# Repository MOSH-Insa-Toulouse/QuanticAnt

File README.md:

# Projet_MOSH 

Auteurs : Quentin Martinez, Nicolas Baudeau, Soufian Yjjou

Caractéristiques de "QuanticAnt" :

Basé sur une arduino, QuanticAnt est un "robot" de petite taille équipé de 4 pattes lui permettant de se déplacer sur le sol.
Les solutions de détections lui permettent d'éviter les obstacles et d'évoluer de façon aléatoire dans une pièce.

QuanticAnt est repoussé par la lumière et emet un son aggaçant quand il se sent bien (peu de lumière ambiante).
Pour prendre le controle de cet insecte l'éclairer directement le force vers une direction donnée.

Mots clés : MARCHE ALEATOIRE, LUMIERE, SANS ROUES, DETECTION D'OBSTACLES

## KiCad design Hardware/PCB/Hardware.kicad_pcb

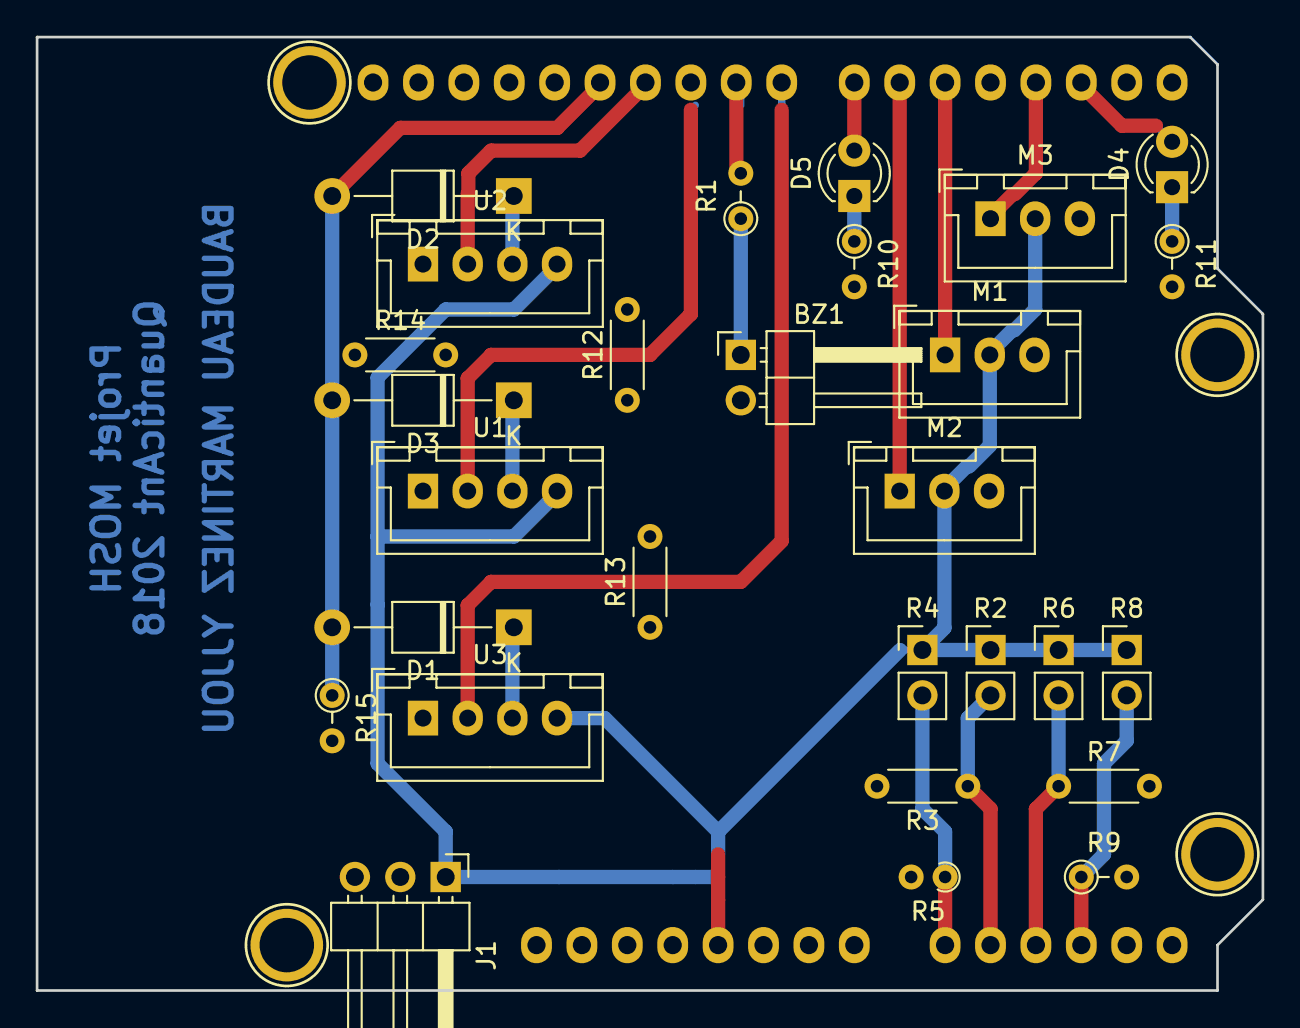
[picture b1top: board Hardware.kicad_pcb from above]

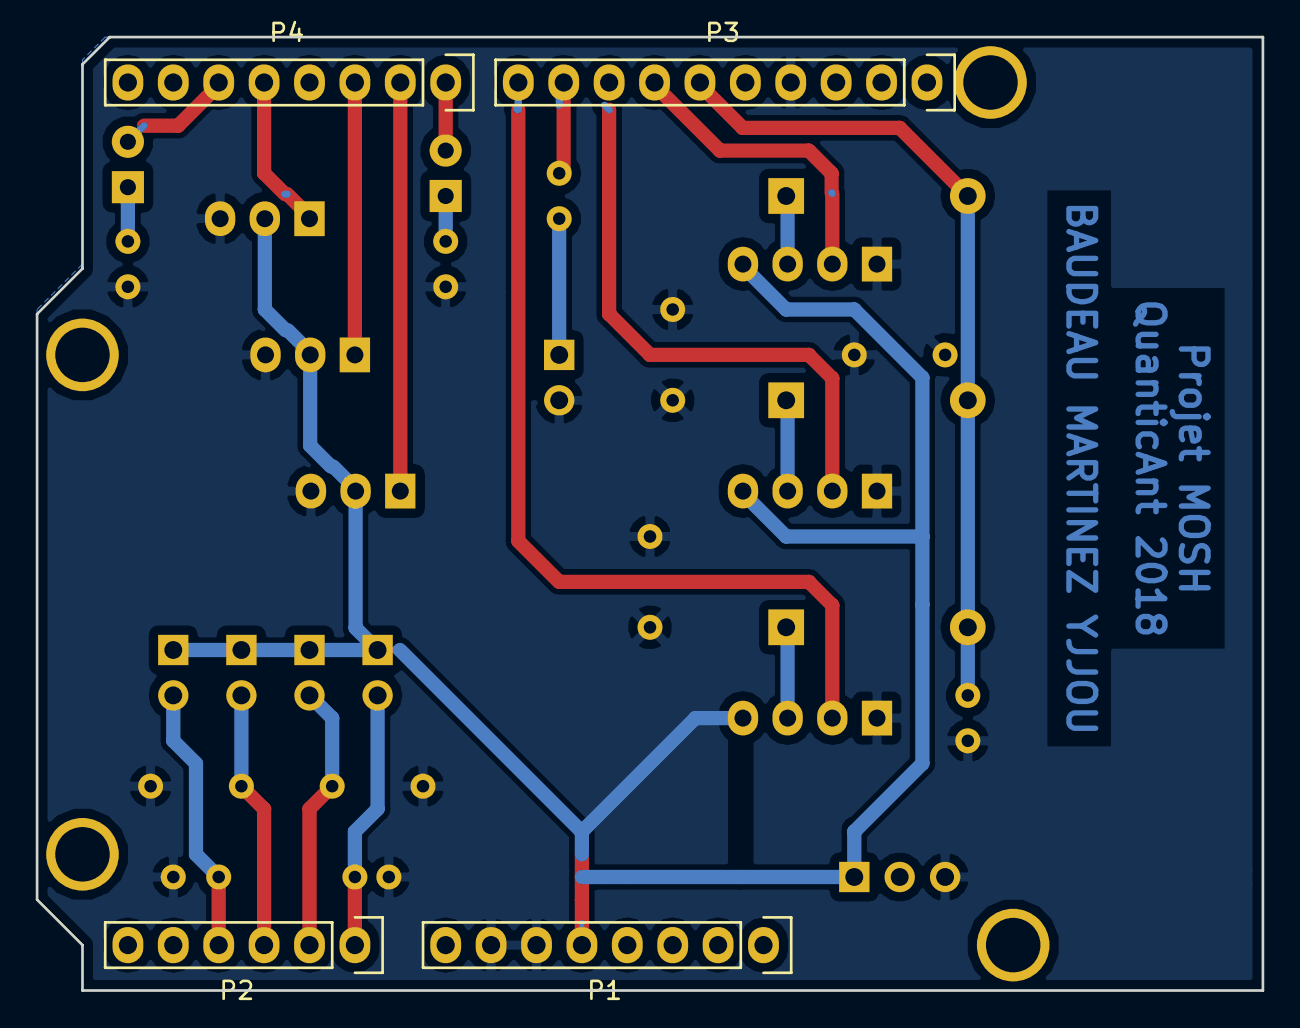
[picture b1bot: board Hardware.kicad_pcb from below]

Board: 2 copper layers, 68.6 x 53.3 mm, 36 parts (4 on the bottom side), 24 nets.

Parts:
BZ1: Buzzer; PinHeader_1x02_P2.54mm_Horizontal
D1, D2, D3: DIODE; D_T-1_P10.16mm_Horizontal
D4, D5: LED; LED_D3.0mm
J1: Conn_01x03_Male; PinHeader_1x03_P2.54mm_Horizontal
M1, M2, M3: Motor_Servo; JST_XH_B03B-XH-A_1x03_P2.50mm_Vertical
P1: Power; Socket_Strip_Arduino_1x08
P2: Analog; Socket_Strip_Arduino_1x06
P3: Digital; Socket_Strip_Arduino_1x10
P4: Digital; Socket_Strip_Arduino_1x08
P5, P6, P7, P8: CONN_01X01; Arduino_1pin
R1, R9, R10, R11, R15: R; R_Axial_DIN0204_L3.6mm_D1.6mm_P2.54mm_Vertical
R2, R4, R6, R8: LDR03; PinHeader_1x02_P2.54mm_Vertical
R3, R7, R12, R13, R14: R; R_Axial_DIN0204_L3.6mm_D1.6mm_P5.08mm_Horizontal
R5: R; R_Axial_DIN0204_L3.6mm_D1.6mm_P1.90mm_Vertical
U1, U2, U3: HC-SR04; JST_XH_B04B-XH-A_1x04_P2.50mm_Vertical

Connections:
+5V: J1.1, M1.2, M2.2, M3.2, P1.5, R2.1, R4.1, R6.1, R8.1, U1.4, U2.4, U3.4
/2: D4.2, P4.6
/3(**): M3.1, P4.5
/5(**): M1.1, P4.3
/6(**): M2.1, P4.2
/7: D5.2, P4.1
/8: P3.10, U3.2
/9(**): P3.9, R1.2
/10(**/SS): P3.8, U1.2
/11(**/MOSI): P3.7, U2.2
/12(MISO): D1.2, D2.2, D3.2, P3.6, R15.1
/A0: P2.1, R4.2, R5.1
/A1: P2.2, R2.2, R3.1
/A2: P2.3, R6.2, R7.1
/A3: P2.4, R8.2, R9.1
/A4(SDA): P2.5, P3.2
/A5(SCL): P2.6, P3.1
GND: BZ1.2, J1.3, M1.3, M2.3, M3.3, P1.6, P1.7, P3.4, R3.2, R5.2, R7.2, R9.2, R10.2, R11.2, R12.1, R12.2, R13.1, R13.2, R14.1, R14.2, R15.2, U1.1, U2.1, U3.1
unnamed: BZ1.1, R1.1
unnamed: D1.1, U3.3
unnamed: D2.1, U2.3
unnamed: D3.1, U1.3
unnamed: D4.1, R11.1
unnamed: D5.1, R10.1

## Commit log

2018-12-05 Deplacement du projet depuis git perso vers git du cours.
2018-12-06 Liste des taches
2018-12-08 Commentaire répartition taches dans code arduino
2018-12-08 Ajout de SERVO.h. Corrections de fonction LUX
2018-12-10 Inversion roles quentin/souf dans le code
2018-12-11 Test Capteurs Lumiere - OK
2018-12-13 Fonction motrice prete
2018-12-13 Ajout de liste des dimensions - MAJ des taches
2018-12-14 Nouveau PCB simplifié
2018-12-14 PCB corrigé et verifié. Typon prêt
2018-12-15 Code testeur UltraSon+Diodes sur PCB Ajout pull down sur la ligne ECHO
2018-12-15 Nouvelle vue 3D
2018-12-15 Create LICENSE
    License file
2018-12-15 Texte sur le pcb pour eviter erreur de gravure
2018-12-16 Update QuanticAnt.ino
    Correction des pins attribués. Ajout de la fonction bruit
2018-12-16 Update QuanticAnt.ino
    Ajout de la fonction motrice et des commandes Leds des yeux.
2018-12-17 Modification epaisseur pistes 0,4mm => 0,8mm (il reste des pistes a grossir)
2018-12-17 corrections mineures
2018-12-17 Premieres modifs apres commentaire de cathy
2018-12-18 PCB final
2018-12-19 Correction comportement erratique moteurs + Fonction US et LUX pris en compte + Tests en environnement hostile
2018-12-19 Quelques commentaires dans le code arduino
2019-01-05 Erreur de pin pour le buzzer corrigee.
2019-01-08 Corrections du comportement face aux obstacles Correction du bruit d'obscurite
2019-01-10 Modif cosmetiques du code. Ajout d'un aleatoire dans la marche 5% tourne droite 5% gauche 90 % devant. Ajout d'un hello world du robot au statup. Ajout d'un meilleur effet random des yeux dans le noi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
2019-01-10 Niveau de nuit en #define plutot que hardcode
2019-01-10 Mise a jour des taches effectuees
2019-01-11 Correction mouvement lent retrait fonction aleatoire
2019-01-11 Dessin shematique
2019-01-13 Correction commentaires code. Ajout images du PCB et du Fritzing. Un peu d'ascii art
2019-01-13 Retrait du document faisant doublon avec le devis.
2019-01-13 Update QuanticAnt.ino
    Correction de commentaires
2019-01-13 Delete 4065fb.pdf
    Document non utilisé pour cette version de QuanticAnt (utilisation du powerbank)
2019-01-15 Ajout Video et presentation projet
